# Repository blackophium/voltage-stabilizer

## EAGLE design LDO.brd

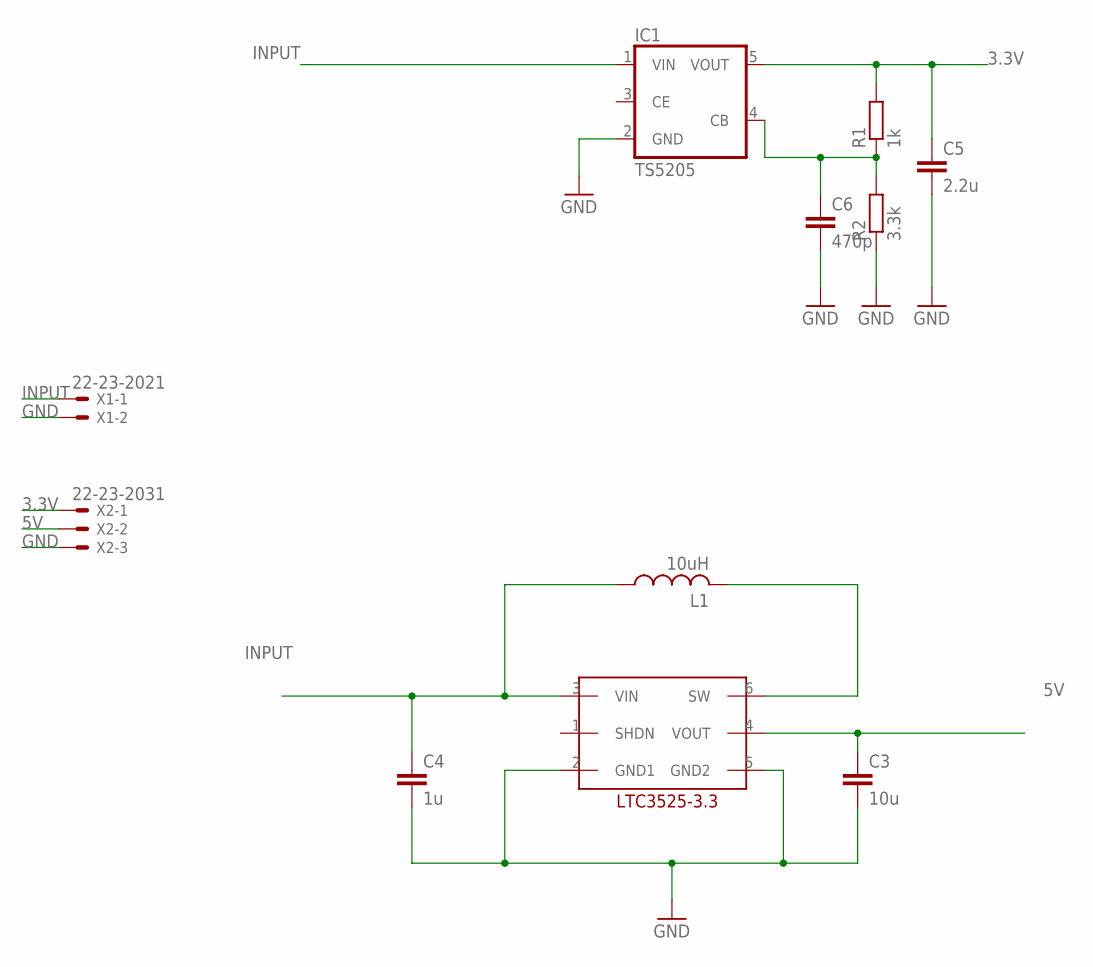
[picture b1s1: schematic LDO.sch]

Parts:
C3: 10u; C0805
C4: 1u; C0805
C5: 2.2u; C0805
C6: 470p; C0805
IC1: TS5205; SOT25
L1: 10uH; L1812
R1: 1k; R0805
R2: 3.3k; R0805
U$1: LTC3525; SC70-6
X1: 22-23-2021
X2: 22-23-2031

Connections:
3.3V: C5.1, IC1.5 (VOUT), R1.2, X2.1
5V: C3.1, U$1.4 (VOUT), X2.2
GND: C3.2, C4.2, C5.2, C6.2, IC1.2 (GND), R2.1, U$1.2 (GND1), U$1.5 (GND2), X1.2, X2.3
INPUT: C4.1, IC1.1 (VIN), L1.1, U$1.3 (VIN), X1.1
unnamed: L1.2, U$1.6 (SW)
unnamed: C6.1, IC1.4 (CB), R1.1, R2.2

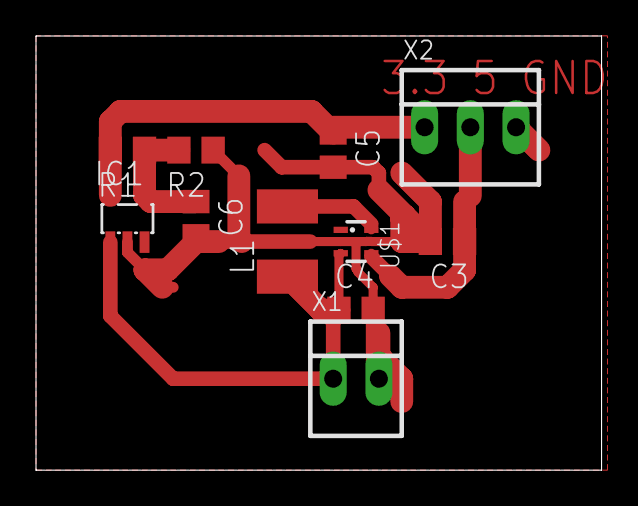
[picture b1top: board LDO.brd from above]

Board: 2 copper layers, 31.4 x 24.1 mm, 11 parts (0 on the bottom side), 6 nets.
